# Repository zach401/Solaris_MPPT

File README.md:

# Solaris_MPPT
A low-cost solar maximum power point tracker. 

#Team
Kyle Crouse | Zeke Zumbro | Austin Ricks | Zachary Lee

#Code
The microprocessor using in this project is the TI MSP430G2553 which is standing in the TI MSP430 Launchpad. C code to run the MPPT using the Perturb and Observe algorithm can be found in the Code folder. This is setup as a TI CodeComposer project.

#Electrical Hardware
Designs for the Cuk DC-DC converter, sensors, and printed circuit board for this project as well as datasheets for components can be found in the Electrical Hardware folder. 
*Note that the PCB design is rev1 which had a few mistakes including miswired pins for the OP-AMP read the Errata file for more info.

#Mechanical Hardware
Designs for a waterproof casing and heat-sink for the design can be found in the Mechanical Hardware folder.

#LTSPICE
Simulations of DC-DC converter and sensors.

#Matlab
Matlab files to calculate component values for Cuk and SEPIC DC-DC converters.

#Final Report Documents
This project was begun as a junior design project at John Brown University, as such, a detailed final report and presentation can be seen in this folder.

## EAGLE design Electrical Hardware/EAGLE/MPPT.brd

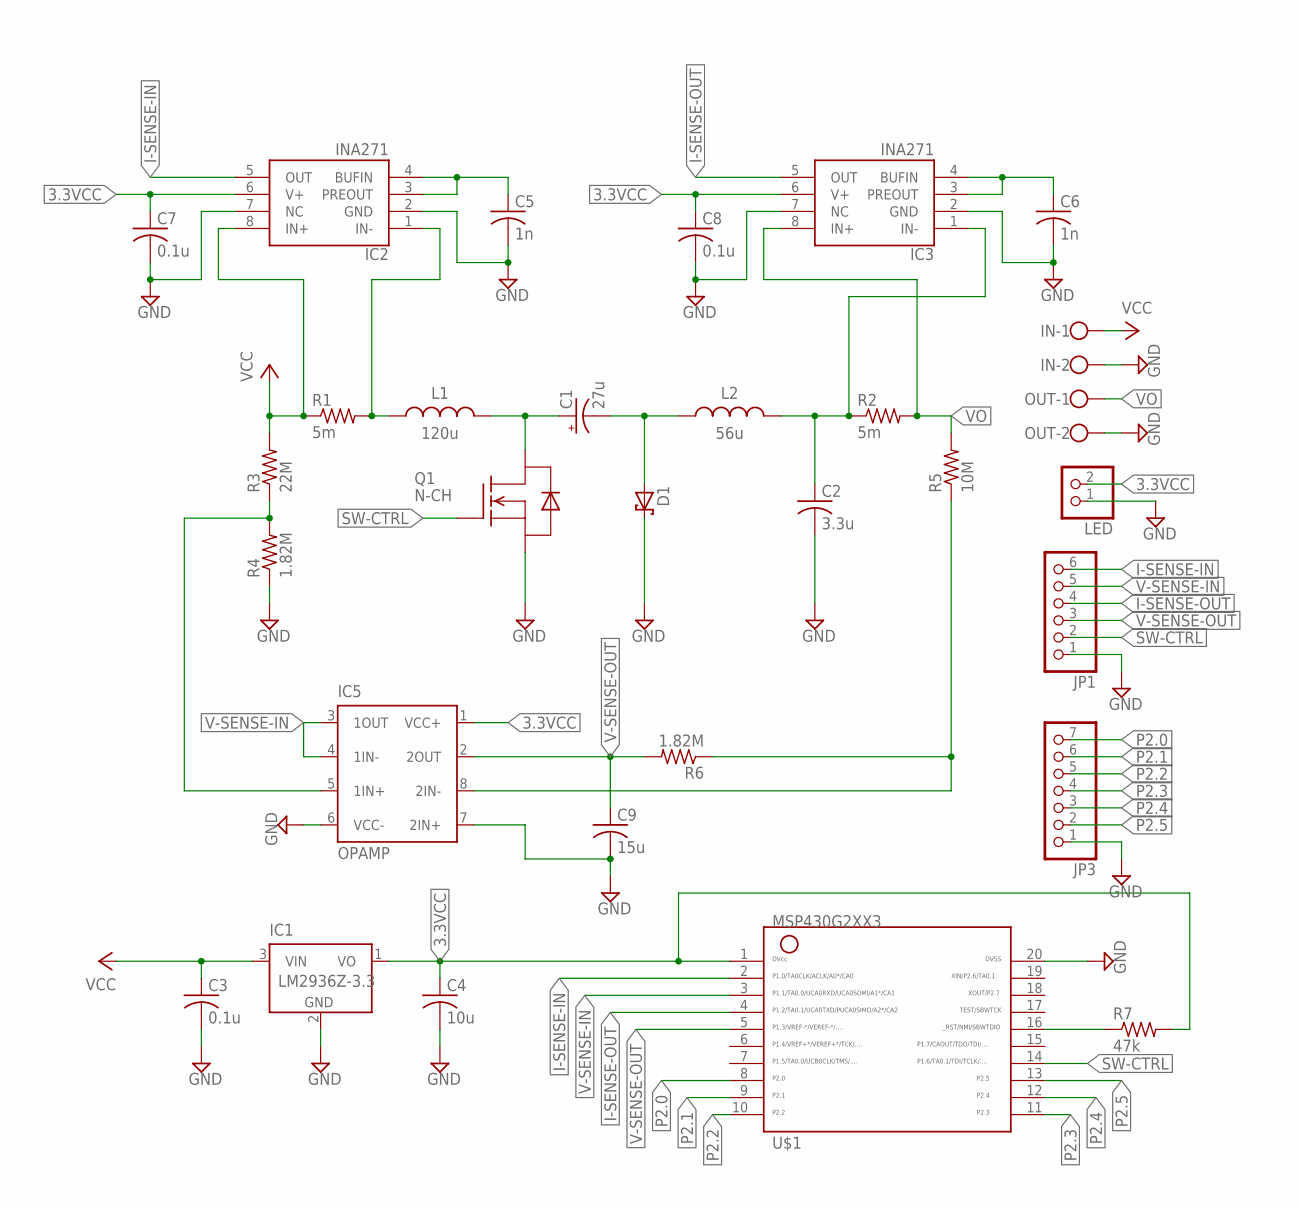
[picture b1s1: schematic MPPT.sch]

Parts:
C1: 27u; E3,5-8
C2: 3.3u; C02,5-03,5X05,5
C3, C7, C8: 0.1u; C050-024X044
C4: 10u; C025-024X044
C5, C6: 1n; C050-045X075
C9: 15u; C050-024X044
D1: SCHOTTKY-DIODEVERTICAL; TO220ACS
IC1: LM2936Z-3.3; TO92
IC2, IC3: INA271; SO08
IC5: OPAMP; DIL08
IN: W237-102
JP1: PINHD-1X6; 1X06
JP3: PINHD-1X7; 1X07
L1: 120u; IND-1140-121K-RC
L2: 56u; IND-2310-RC-VERT
LED: PINHD-1X2; 1X02
OUT: W237-102
Q1: N-CH; TO220-VERT
R1, R2: 5m; BR3-CURRENT-SENSE
R3: 22M; 0309/12
R4, R6: 1.82M; 0207/10
R5: 10M; 0309/12
R7: 47k; 0207/7
U$1: G2553; N20

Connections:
3.3VCC: C4.1, C7.1, C8.1, IC1.1 (VO), IC2.6 (V+), IC3.6 (V+), IC5.1 (VCC+), LED.2, R7.2, U$1.1
GND: C2.2, C3.2, C4.2, C5.2, C6.2, C7.2, C8.2, C9.2, D1.C, IC1.2 (GND), IC2.2 (GND), IC2.7 (NC), IC3.2 (GND), IC3.7 (NC), IC5.6 (VCC-), IC5.7 (2IN+), IN.2, JP1.1, JP3.1, LED.1, OUT.2, Q1.P$3 (S), R4.1, U$1.20
I-SENSE-IN: IC2.5 (OUT), JP1.6, U$1.2
I-SENSE-OUT: IC3.5 (OUT), JP1.4, U$1.4
unnamed: C1.+, L1.P$2, Q1.P$2 (D)
unnamed: C1.-, D1.A, L2.P$1
unnamed: R7.1, U$1.16
unnamed: IC5.5 (1IN+), R3.1, R4.2
unnamed: IC5.8 (2IN-), R5.1, R6.1
unnamed: IC2.1 (IN-), L1.P$1, R1.P$2 (2)
unnamed: C2.1, IC3.1 (IN-), L2.P$2, R2.P$1 (1)
unnamed: C5.1, IC2.3 (PREOUT), IC2.4 (BUFIN)
unnamed: C6.1, IC3.3 (PREOUT), IC3.4 (BUFIN)
P2.0: JP3.7, U$1.8
P2.1: JP3.6, U$1.9
P2.2: JP3.5, U$1.10
P2.3: JP3.4, U$1.11
P2.4: JP3.3, U$1.12
P2.5: JP3.2, U$1.13
SW-CTRL: JP1.2, Q1.P$1 (G), U$1.14
V-SENSE-IN: IC5.3 (1OUT), IC5.4 (1IN-), JP1.5, U$1.3
V-SENSE-OUT: C9.1, IC5.2 (2OUT), JP1.3, R6.2, U$1.5
VCC: C3.1, IC1.3 (VIN), IC2.8 (IN+), IN.1, R1.P$1 (1), R3.2
VO: IC3.8 (IN+), OUT.1, R2.P$2 (2), R5.2

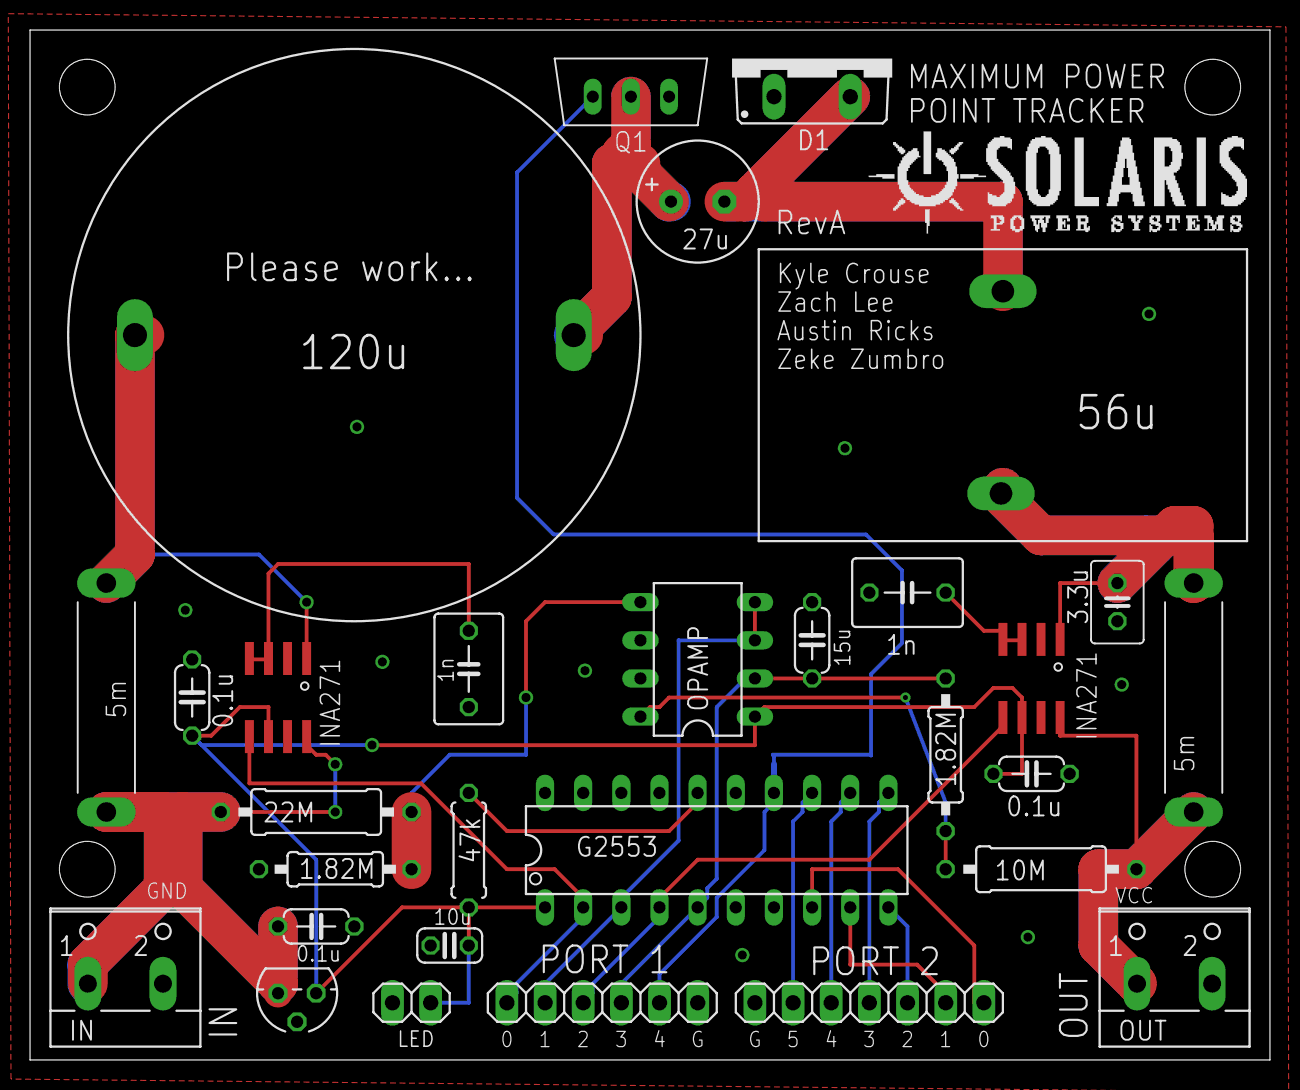
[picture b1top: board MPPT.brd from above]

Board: 2 copper layers, 82.6 x 68.6 mm, 30 parts (0 on the bottom side), 24 nets.

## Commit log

2015-09-25 Added initial project files.
